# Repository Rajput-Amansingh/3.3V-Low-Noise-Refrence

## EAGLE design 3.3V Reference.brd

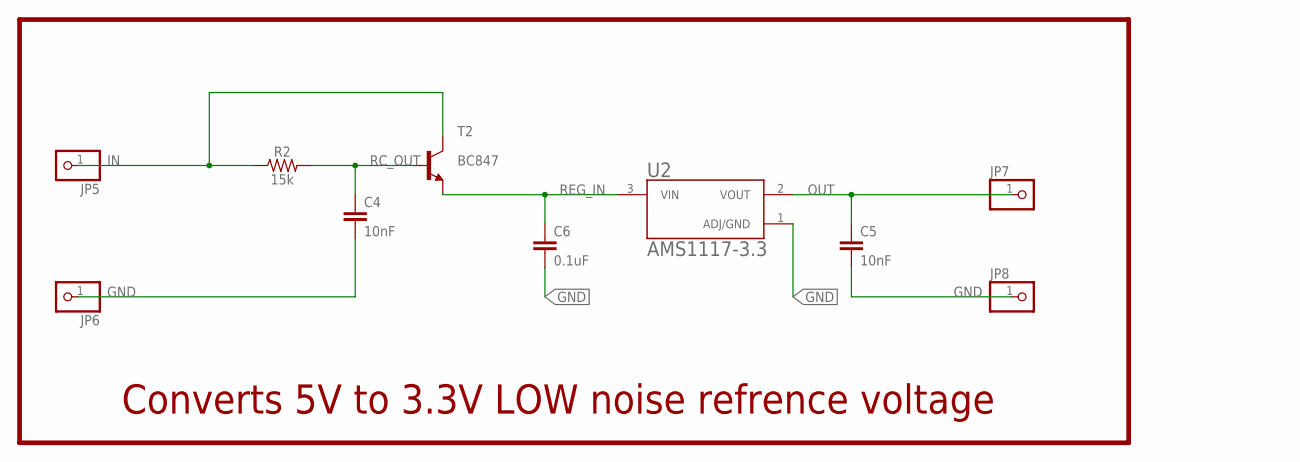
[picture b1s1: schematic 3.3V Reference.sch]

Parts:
C4, C5: 10nF; 0603
C6: 0.1uF; 0603
JP5, JP6, JP7, JP8: PINHD-1X1; 1X01
R2: 15k; 0603
T2: BC847; SOT23
U2: AMS1117-3.3; SOT229P700X180-4N

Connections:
GND: C4.2, C5.2, C6.2, JP6.1, JP8.1, U2.1 (ADJ/GND)
IN: JP5.1, R2.1, T2.3 (C)
OUT: C5.1, JP7.1, U2.2 (VOUT)
RC_OUT: C4.1, R2.2, T2.1 (B)
REG_IN: C6.1, T2.2 (E), U2.3 (VIN)

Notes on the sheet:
Converts 5V to 3.3V LOW noise refrence voltage

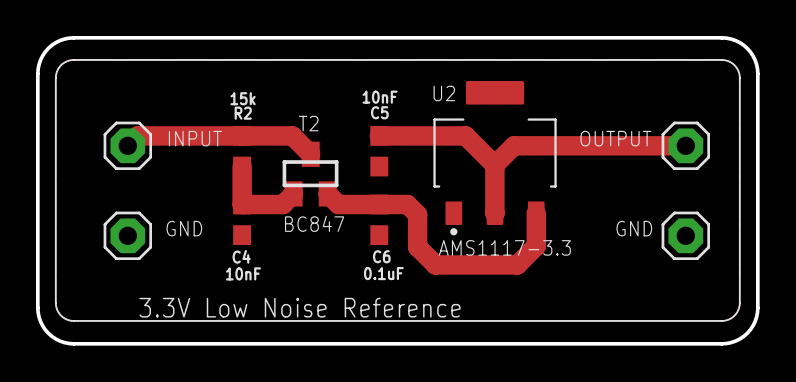
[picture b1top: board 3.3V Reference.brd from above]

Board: 2 copper layers, 40.0 x 17.0 mm, 10 parts (0 on the bottom side), 5 nets.

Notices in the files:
parts and their libraries:
SparkFun-Resistors: Licensing: Creative Commons ShareAlike 4.0 International - https://creativecommons.org/licenses/by-sa/4.0
